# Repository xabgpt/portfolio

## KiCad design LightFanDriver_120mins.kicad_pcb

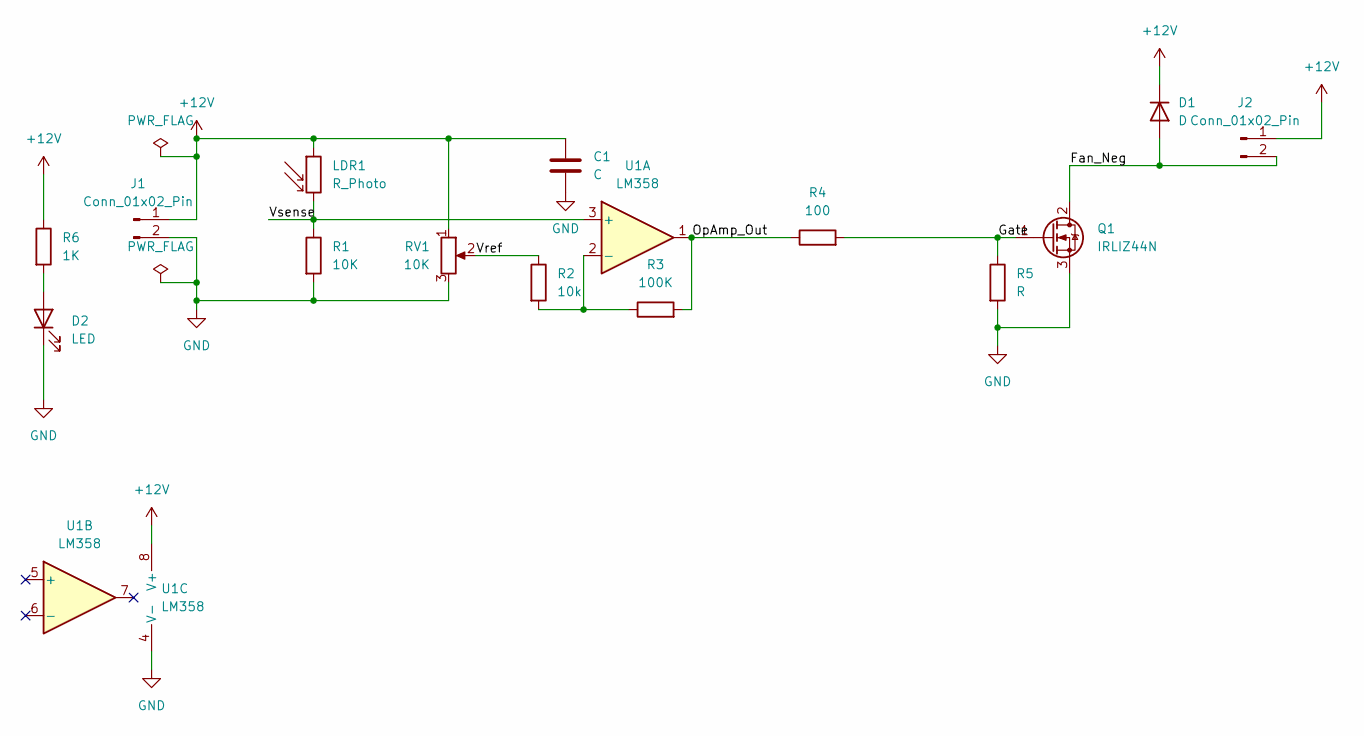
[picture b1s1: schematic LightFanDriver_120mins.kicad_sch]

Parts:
C1: C; C_Disc_D5.0mm_W2.5mm_P2.50mm
D1: D; D_DO-41_SOD81_P10.16mm_Horizontal
D2: LED
J1, J2: Conn_01x02_Pin; PinHeader_1x02_P2.54mm_Vertical
LDR1: R_Photo; R_Axial_DIN0207_L6.3mm_D2.5mm_P10.16mm_Horizontal
Q1: IRLIZ44N; TO-220F-3_Vertical
R1: 10K; R_Axial_DIN0207_L6.3mm_D2.5mm_P10.16mm_Horizontal
R2: 10k; R_Axial_DIN0207_L6.3mm_D2.5mm_P10.16mm_Horizontal
R3: 100K; R_Axial_DIN0207_L6.3mm_D2.5mm_P10.16mm_Horizontal
R4: 100; R_Axial_DIN0207_L6.3mm_D2.5mm_P10.16mm_Horizontal
R5: R; R_Axial_DIN0207_L6.3mm_D2.5mm_P10.16mm_Horizontal
R6: 1K
RV1: 10K; Potentiometer_Bourns_3386P_Vertical
U1: LM358; DIP-8_W7.62mm

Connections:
+12V: C1.1, D1.1 (K), J1.1, J2.1, LDR1.1, R6.1, RV1.1, U1.8 (V+)
/Fan_Neg: D1.2 (A), J2.2, Q1.2 (D)
/Gate: Q1.1 (G), R4.2, R5.1
/OpAmp_Out: R3.2, R4.1, U1.1
/Vref: R2.1, RV1.2
/Vsense: LDR1.2, R1.1, U1.3 (+)
GND: C1.2, D2.1 (K), J1.2, Q1.3 (S), R1.2, R5.2, RV1.3, U1.4 (V-)
unnamed: D2.2 (A), R6.2
unnamed: R2.2, R3.1, U1.2 (-)

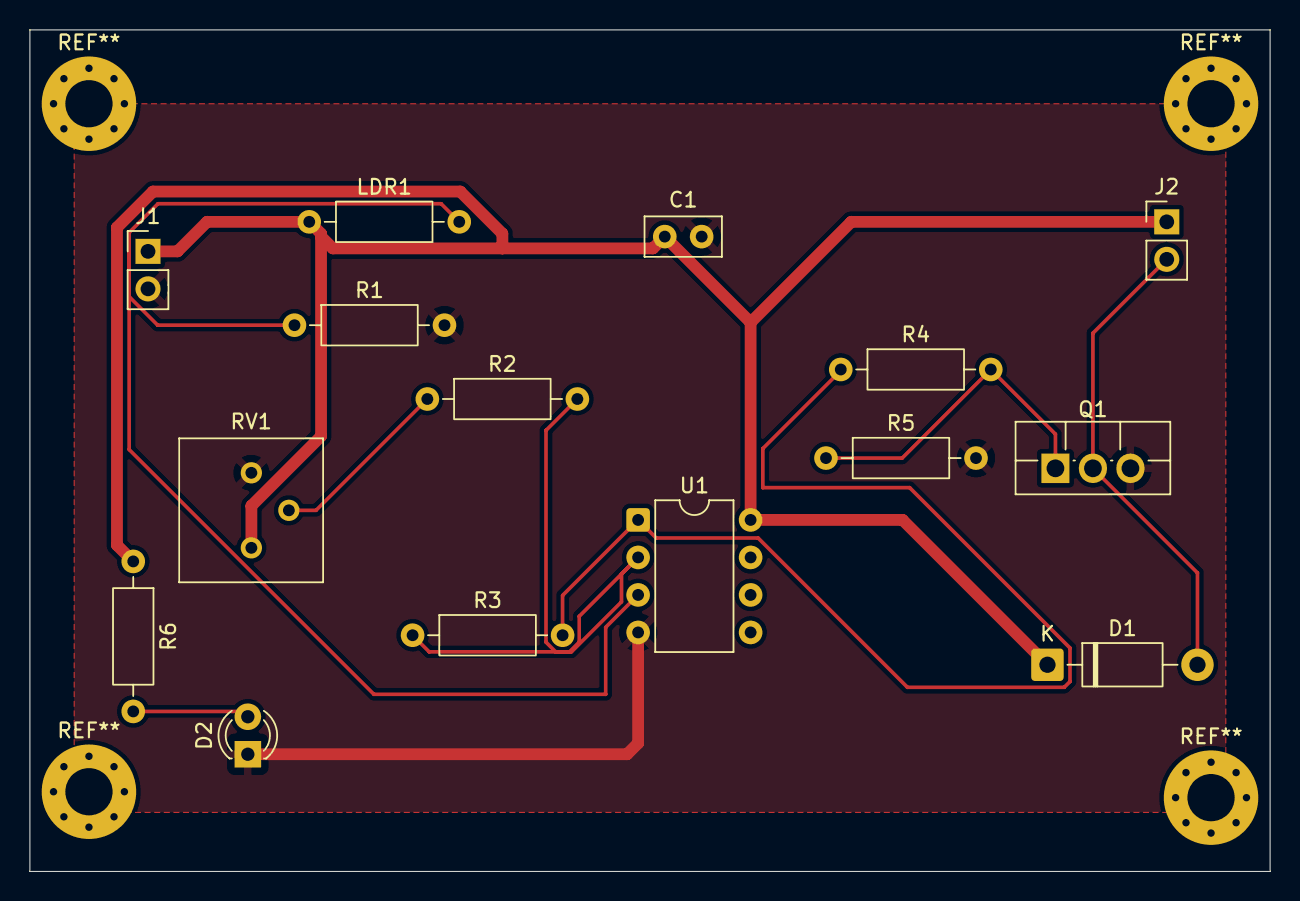
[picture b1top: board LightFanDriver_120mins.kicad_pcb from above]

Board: 2 copper layers, 84.0 x 57.0 mm, 15 parts (0 on the bottom side), 9 nets.

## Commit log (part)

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2026-03-25 Initial commit: Portfolio files
2026-03-25 Update testimonials & site improvements: SEO, favicon, mobile nav, mailto form
2026-03-25 Add interactive 12V PSU simulation report embedded in portfolio
2026-03-25 Add interactive DC-DC buck converter simulation report
